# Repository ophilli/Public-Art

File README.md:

# Public-Art

This is code for a depiction of the Clemson Bike Share system.

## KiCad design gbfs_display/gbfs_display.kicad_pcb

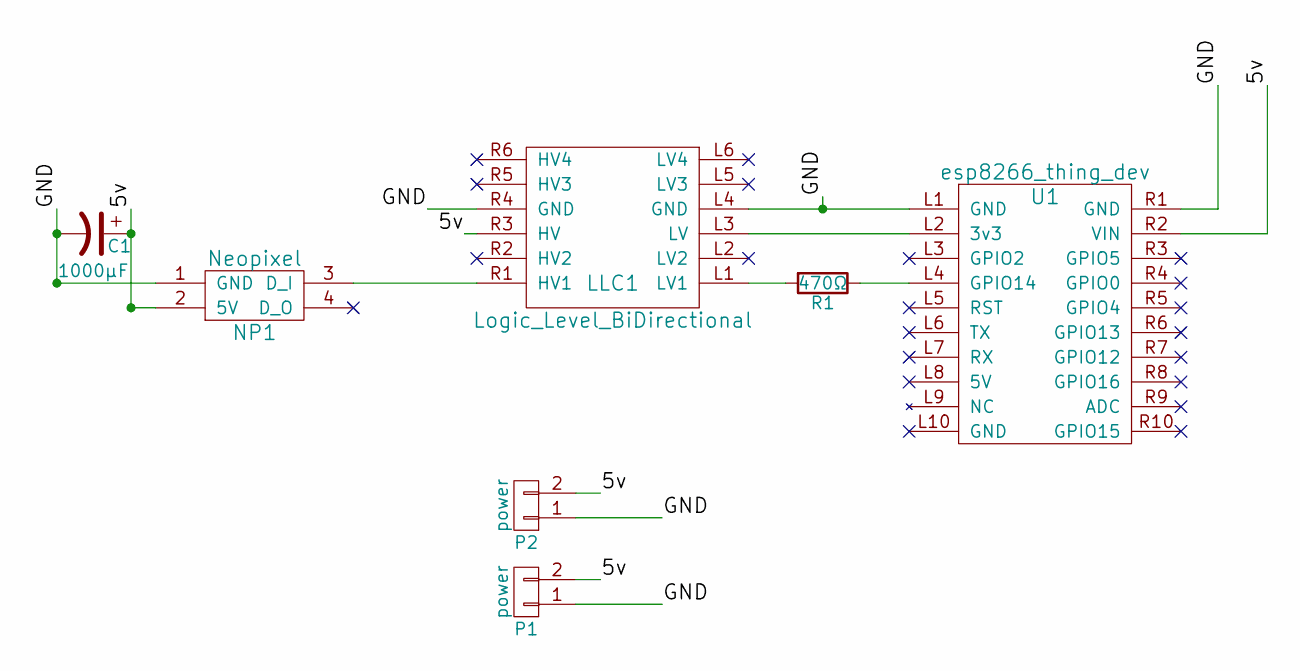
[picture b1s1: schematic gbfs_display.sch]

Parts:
C1: 1000µF; CP_Radial_D10.0mm_P5.00mm
LLC1: Logic_Level_BiDirectional; Logic_Level_Bidirectional
NP1: Neopixel; NeoConnect_SolderWirePad_3x_2-5mmDrill
P1, P2: power; Power_SolderWirePad_2x_2-5mmDrill
R1: 470Ω; R_Axial_DIN0204_L3.6mm_D1.6mm_P7.62mm_Horizontal
U1: esp8266_thing_dev; esp8266_thing

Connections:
/5v: C1.1, LLC1.R3 (HV), NP1.2 (5V), P1.2, P2.2, U1.R2 (VIN)
/GND: C1.2, LLC1.L4 (GND), LLC1.R4 (GND), NP1.1 (GND), P1.1, P2.1, U1.L1 (GND), U1.R1 (GND)
unnamed: LLC1.L1 (LV1), R1.2
unnamed: LLC1.L3 (LV), U1.L2 (3v3)
unnamed: LLC1.R1 (HV1), NP1.3 (D_I)
unnamed: R1.1, U1.L4 (GPIO14)

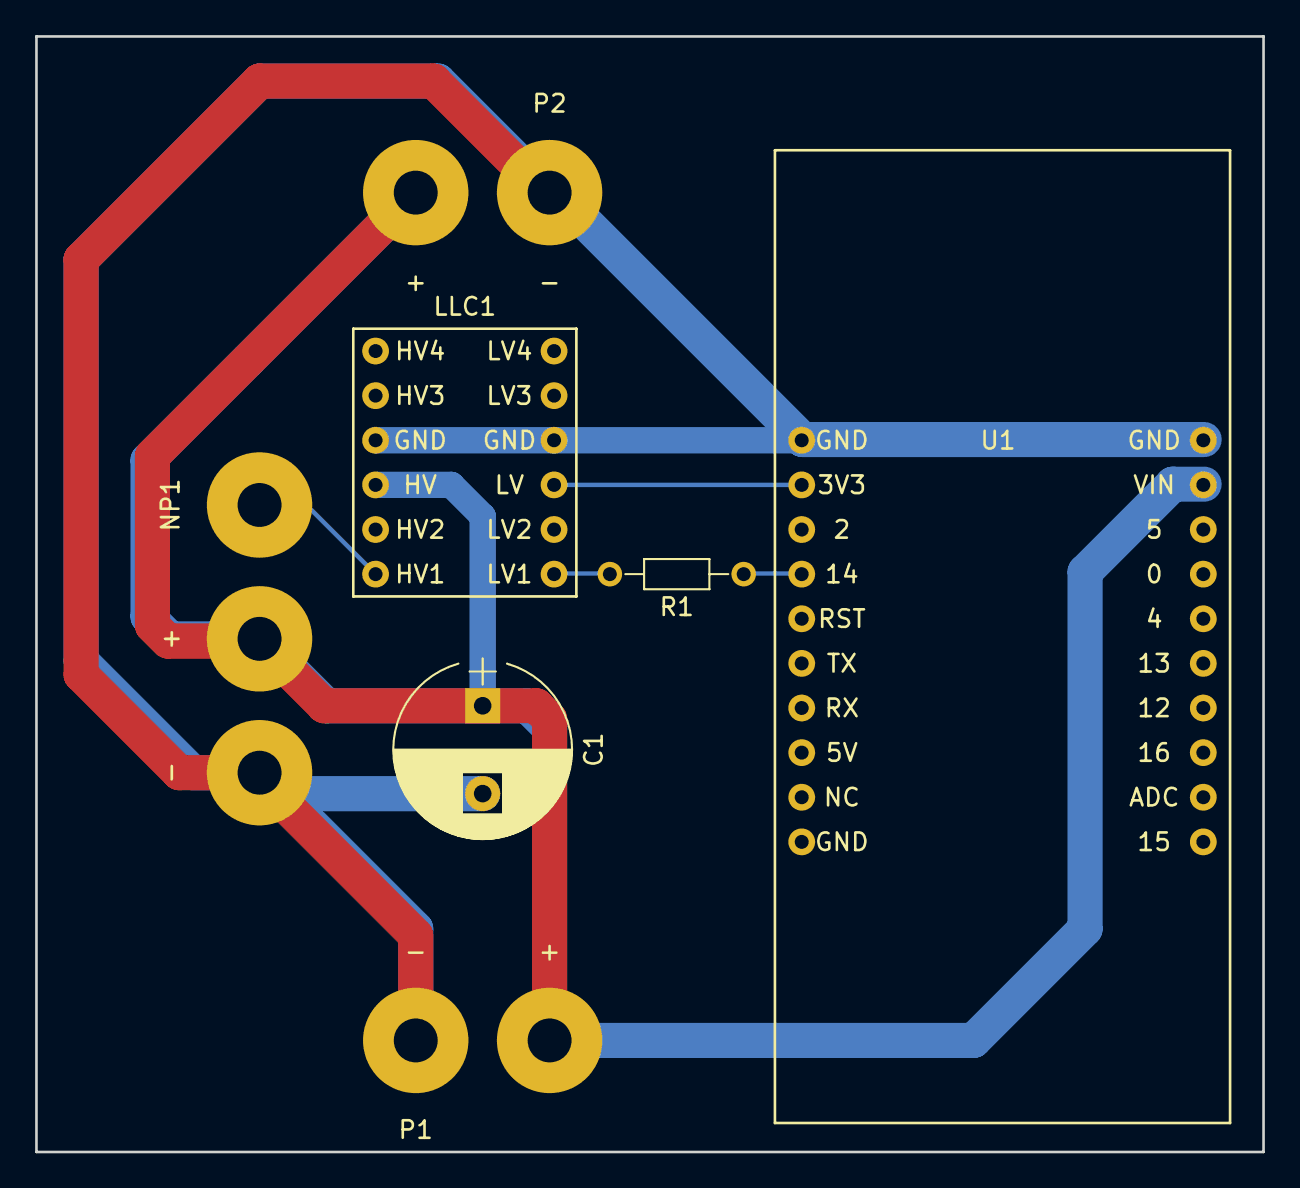
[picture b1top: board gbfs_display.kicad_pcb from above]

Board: 2 copper layers, 69.8 x 63.5 mm, 7 parts (0 on the bottom side), 6 nets.

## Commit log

2017-11-11 :lollipop: Added .gitattributes & .gitignore files
2017-11-11 Schematic for gbfs_display
2017-11-11 First draft of ESP8266_Thing footprint
2017-11-11 Draw up Logic Level Convertor
2017-11-11 Remove neopixels and add footprints
2017-11-11 New Footprint for the cable
2017-11-11 Add power to schematic
2017-11-14 Wrap up First Draft of Board
2017-11-14 Gerbers for first draft
    Should I be committing these? Not sure.
2017-12-02 Upload Bikeshare Code
2018-03-01 Create LICENSE
2018-09-12 Update PCB (I don't know what changed)
    Committing this because it was saved - I honestly don't know what was
    changed about it.
2018-09-12 clean up station var naming
2018-09-13 Create NeoPixel_Ring class
    This is a refactor that moves the interface with the Neopixel rings to a
    class - making it easier to be clear about which data goes into which
    ring.
